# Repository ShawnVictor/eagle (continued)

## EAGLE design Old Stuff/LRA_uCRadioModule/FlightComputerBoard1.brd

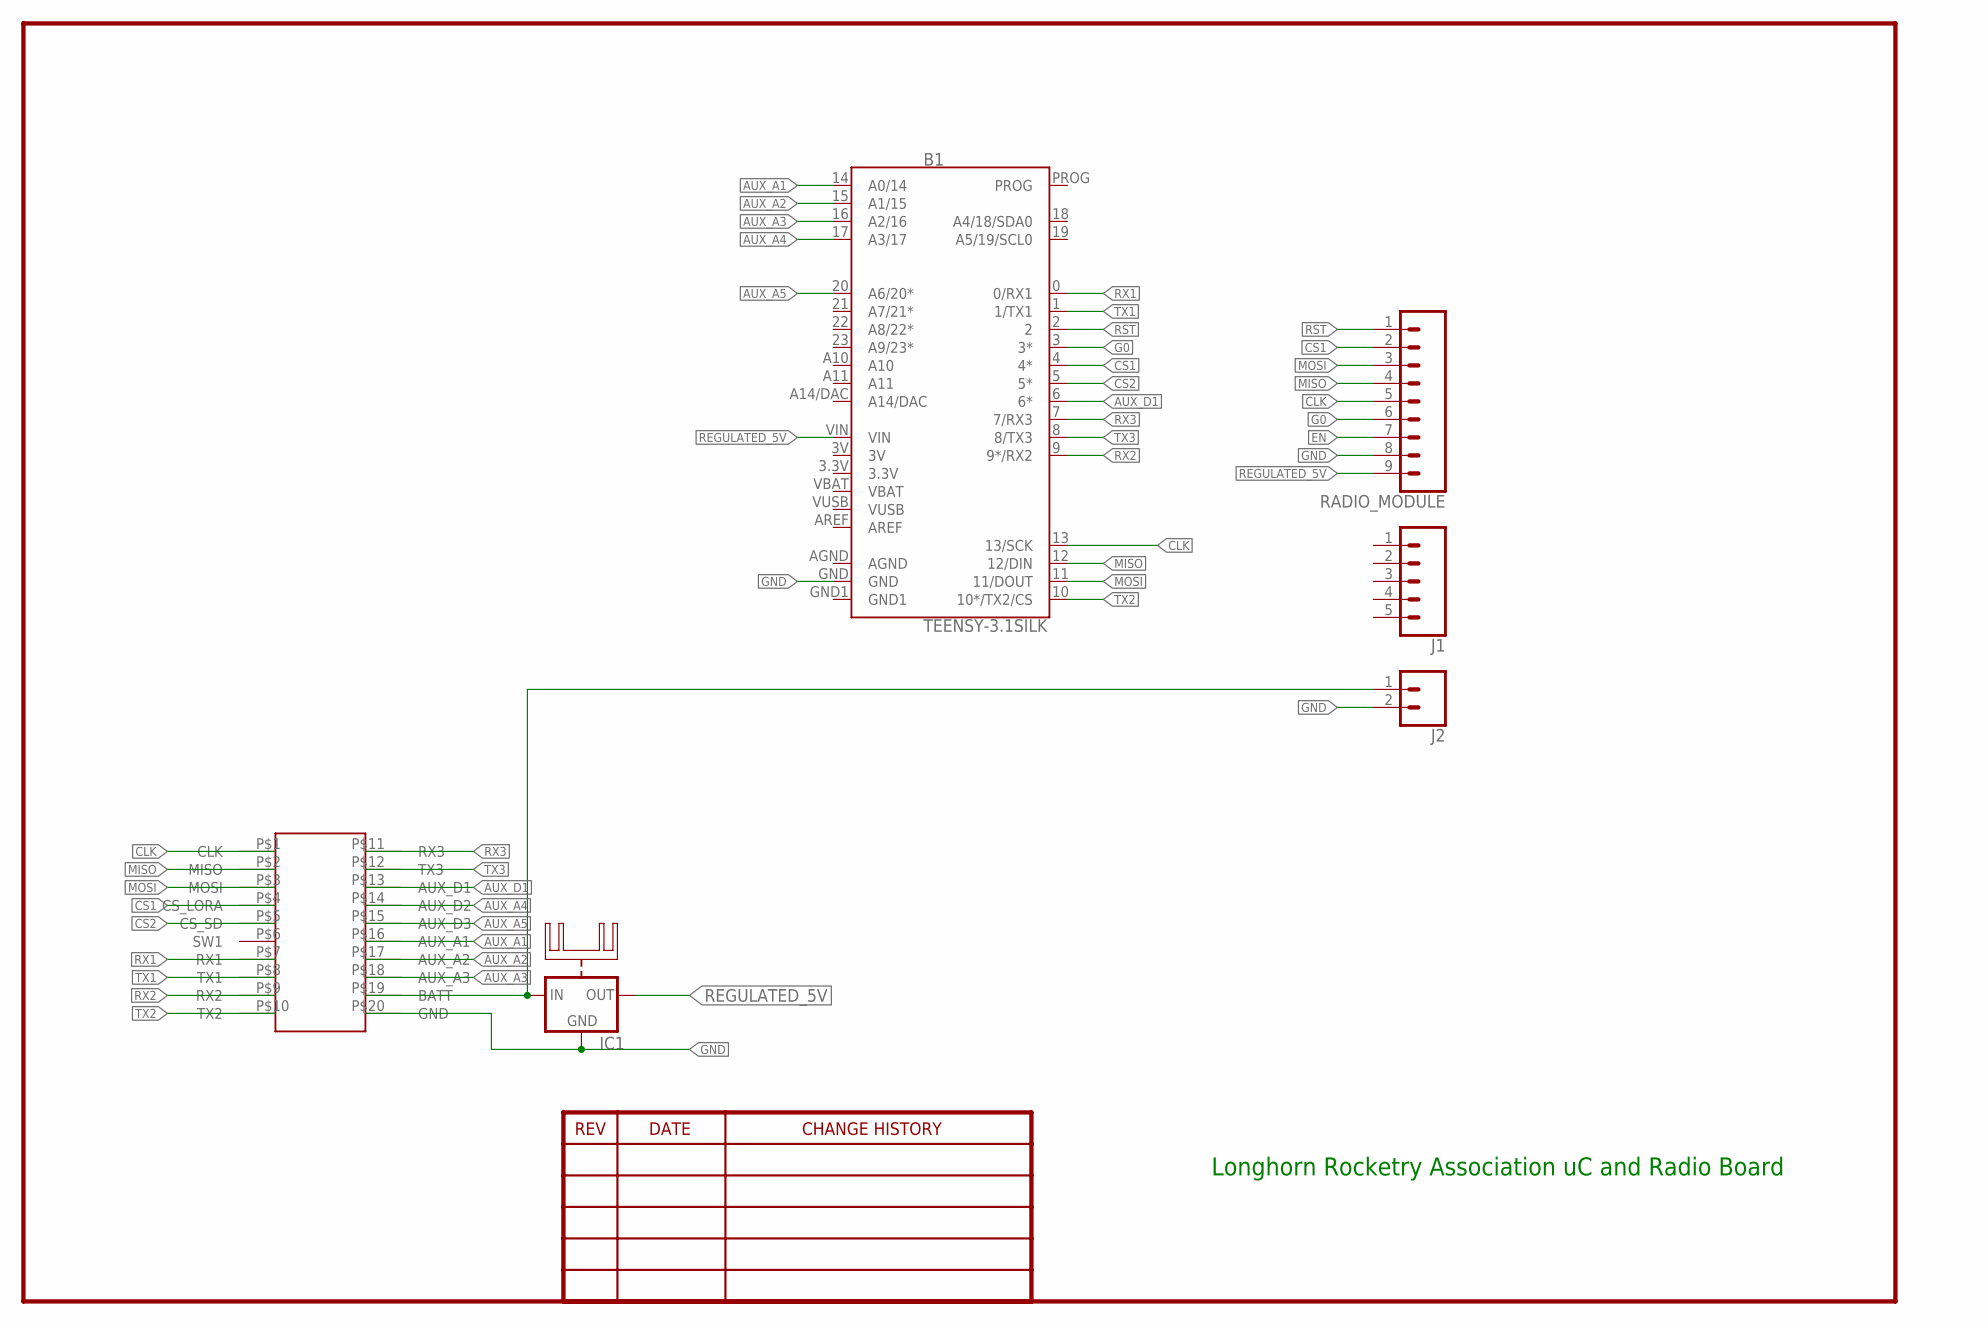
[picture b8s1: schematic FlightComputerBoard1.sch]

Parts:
B1: TEENSY-3.1SILK; TEENSY-3.1
IC1: 78XXH
J1: CONN_05; 1X05
J2: CONN_02; 1X02
RADIO_MODULE: CONN_09; 1X09
U$1: SMALLHEADERPACKAGE

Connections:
3.3V: B1.3.3V
3V: B1.3V
AGND: B1.AGND
AUX_A1: B1.14 (A0/14), U$1.P$16 (AUX_A1)
AUX_A2: B1.15 (A1/15), U$1.P$17 (AUX_A2)
AUX_A3: B1.16 (A2/16), U$1.P$18 (AUX_A3)
AUX_A4: B1.17 (A3/17), U$1.P$14 (AUX_D2)
AUX_A5: B1.20 (A6/20*), U$1.P$15 (AUX_D3)
AUX_D1: B1.6 (6*), U$1.P$13 (AUX_D1)
CLK: B1.13 (13/SCK), RADIO_MODULE.5, U$1.P$1 (CLK)
CS1: B1.4 (4*), RADIO_MODULE.2, U$1.P$4 (CS_LORA)
CS2: B1.5 (5*), U$1.P$5 (CS_SD)
EN: RADIO_MODULE.7
G0: B1.3 (3*), RADIO_MODULE.6
GND: B1.GND, IC1.GND, J2.2, RADIO_MODULE.8, U$1.P$20 (GND)
GND1: B1.GND1
MISO: B1.12 (12/DIN), RADIO_MODULE.4, U$1.P$2 (MISO)
MOSI: B1.11 (11/DOUT), RADIO_MODULE.3, U$1.P$3 (MOSI)
unnamed: IC1.IN, J2.1, U$1.P$19 (BATT)
REGULATED_5V: B1.VIN, IC1.OUT, RADIO_MODULE.9
RST: B1.2, RADIO_MODULE.1
RX1: B1.0 (0/RX1), U$1.P$7 (RX1)
RX2: B1.9 (9*/RX2), U$1.P$9 (RX2)
RX3: B1.7 (7/RX3), U$1.P$11 (RX3)
TX1: B1.1 (1/TX1), U$1.P$8 (TX1)
TX2: B1.10 (10*/TX2/CS), U$1.P$10 (TX2)
TX3: B1.8 (8/TX3), U$1.P$12 (TX3)
VBAT: B1.VBAT
VUSB: B1.VUSB

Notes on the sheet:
Longhorn Rocketry Association uC and Radio Board

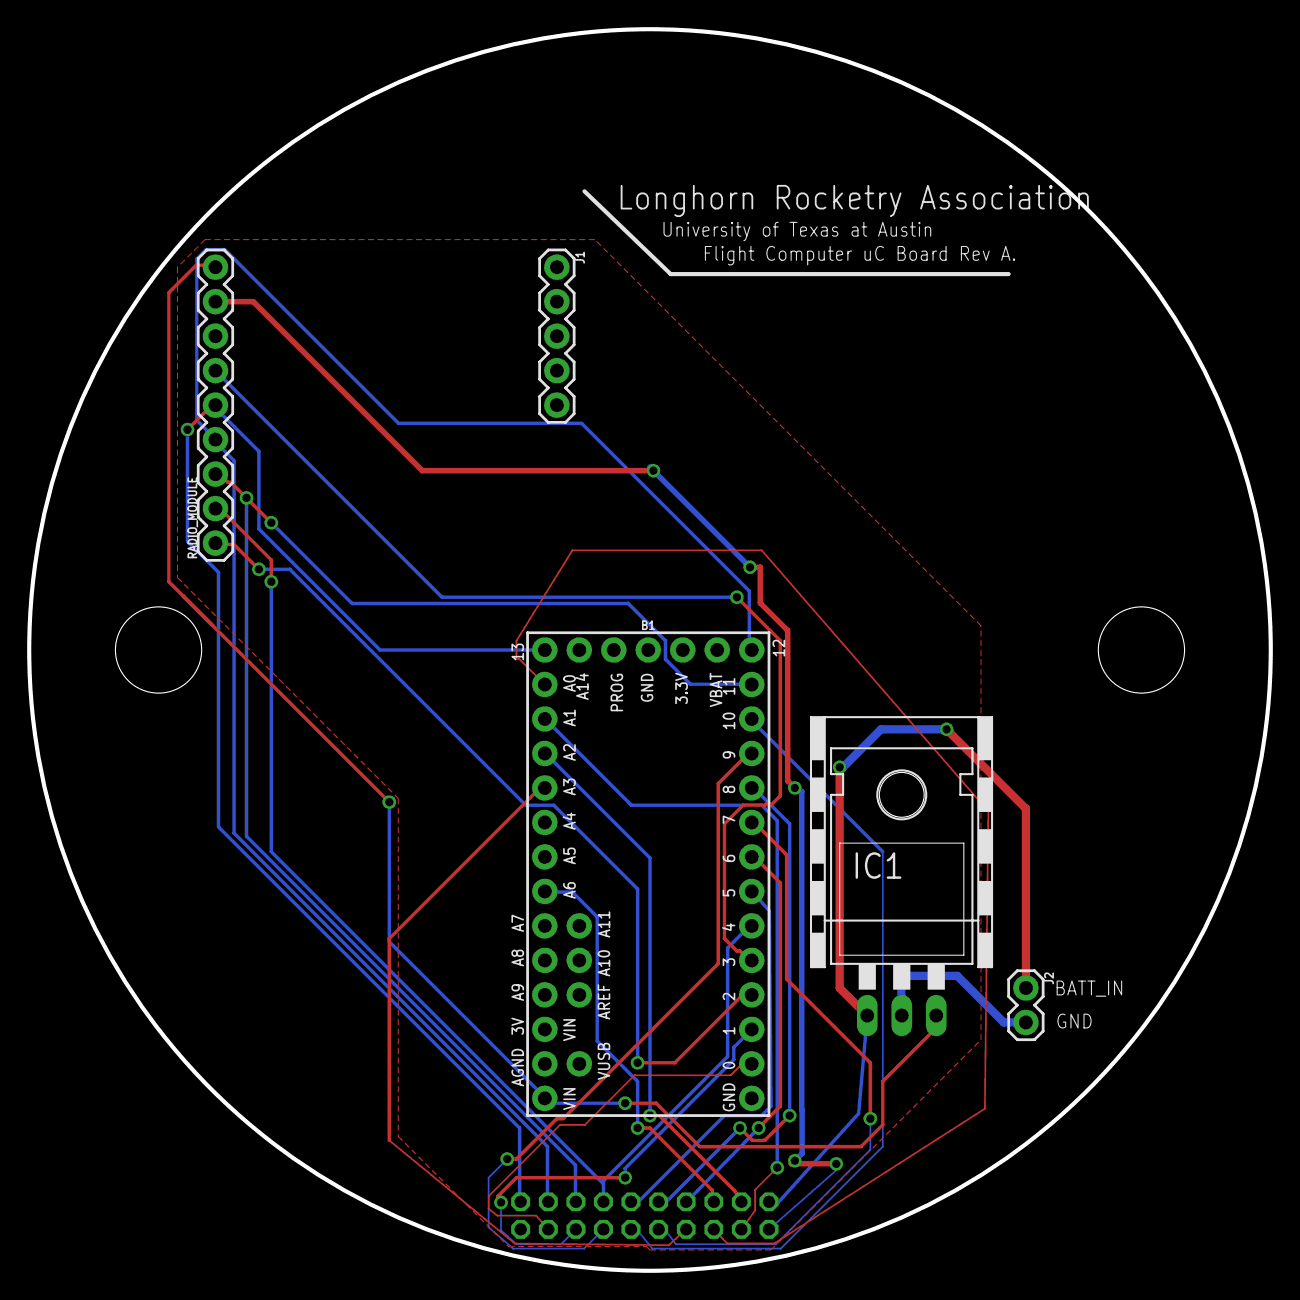
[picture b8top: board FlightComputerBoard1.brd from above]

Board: 2 copper layers, 91.4 x 91.4 mm, 6 parts (0 on the bottom side), 22 nets.
